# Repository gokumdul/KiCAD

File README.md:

# KiCAD
PCB sketch(.sch), and gerberData (.gbr)

- Project List
1. Simple LED and simple resistor
2. Multiple LEDs and multiple resistors
3. Fire alarm system

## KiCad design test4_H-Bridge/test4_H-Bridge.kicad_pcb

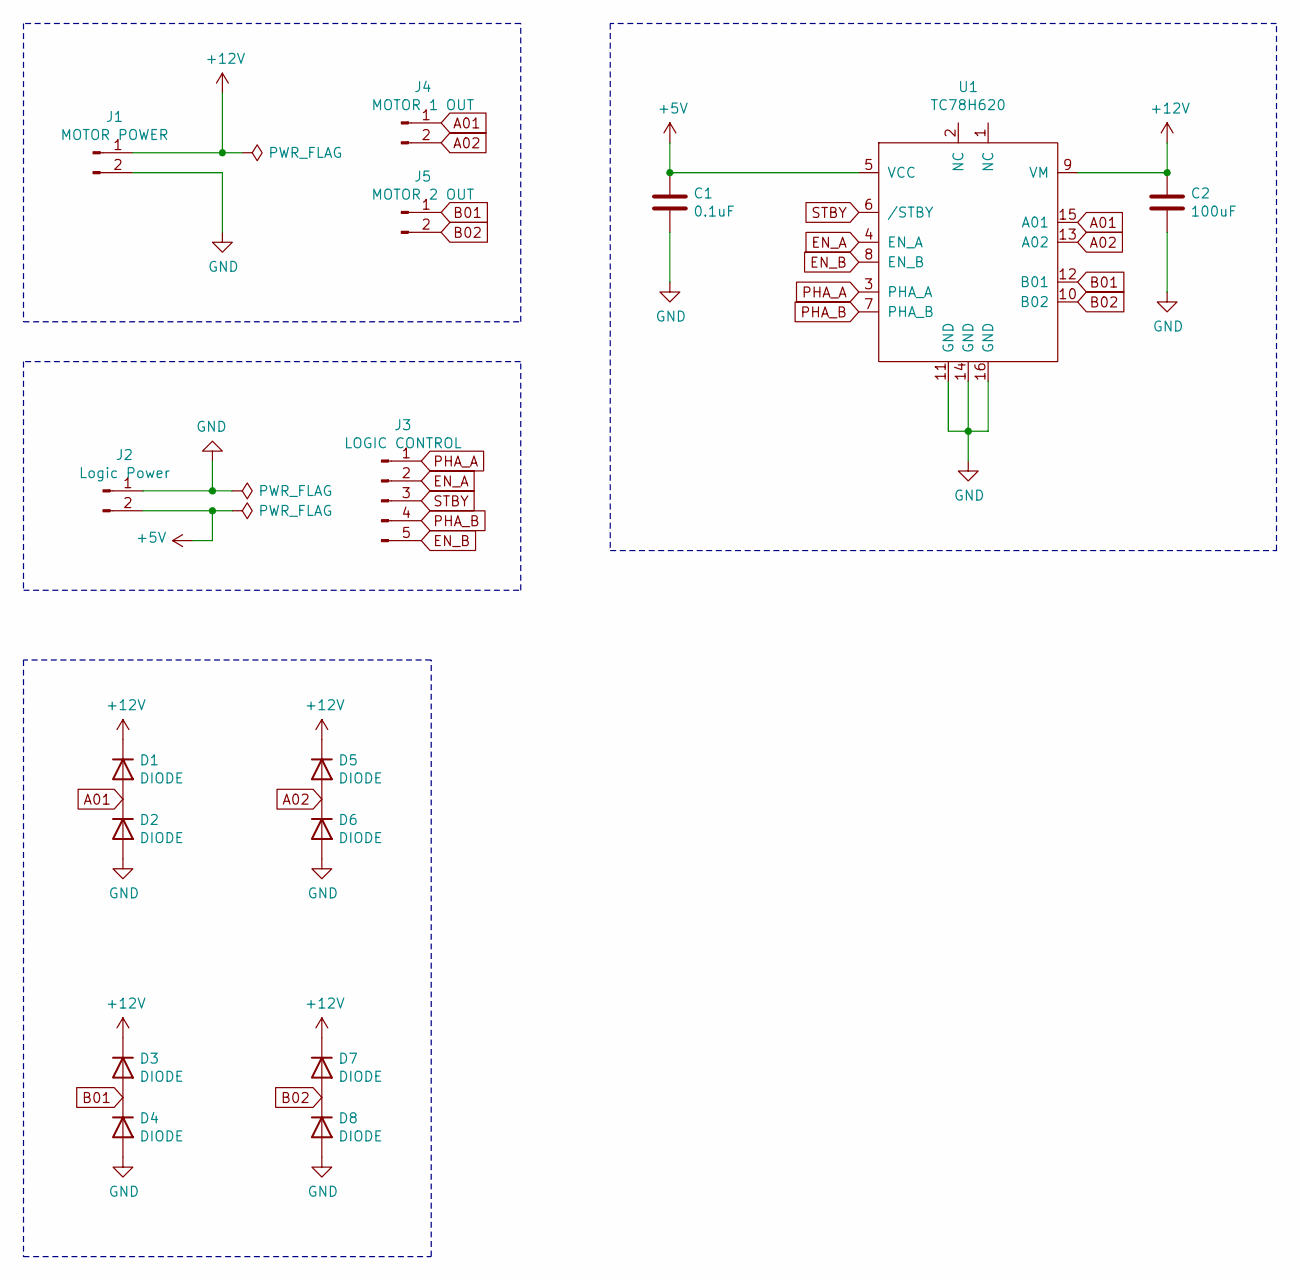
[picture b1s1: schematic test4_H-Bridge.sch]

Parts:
C1: 0.1uF
C2: 100uF
D1, D2, D3, D4, D5, D6, D7, D8: DIODE
J1: MOTOR POWER
J2: Logic Power
J3: LOGIC CONTROL
J4: MOTOR 1 OUT
J5: MOTOR 2 OUT
U1: TC78H620

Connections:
+5V: C1.2, J2.2, U1.5 (VCC)
+12V: C2.2, D1.2 (K), D3.2 (K), D5.2 (K), D7.2 (K), J1.1, U1.9 (VM)
A01: D1.1 (A), D2.2 (K), J4.1, U1.15 (A01)
A02: D5.1 (A), D6.2 (K), J4.2, U1.13 (A02)
B01: D3.1 (A), D4.2 (K), J5.1, U1.12 (B01)
B02: D7.1 (A), D8.2 (K), J5.2, U1.10 (B02)
EN_A: J3.2, U1.4 (EN_A)
EN_B: J3.5, U1.8 (EN_B)
GND: C1.1, C2.1, D2.1 (A), D4.1 (A), D6.1 (A), D8.1 (A), J1.2, J2.1, U1.11 (GND), U1.14 (GND), U1.16 (GND)
PHA_A: J3.1, U1.3 (PHA_A)
PHA_B: J3.4, U1.7 (PHA_B)
STBY: J3.3, U1.6 (/STBY)

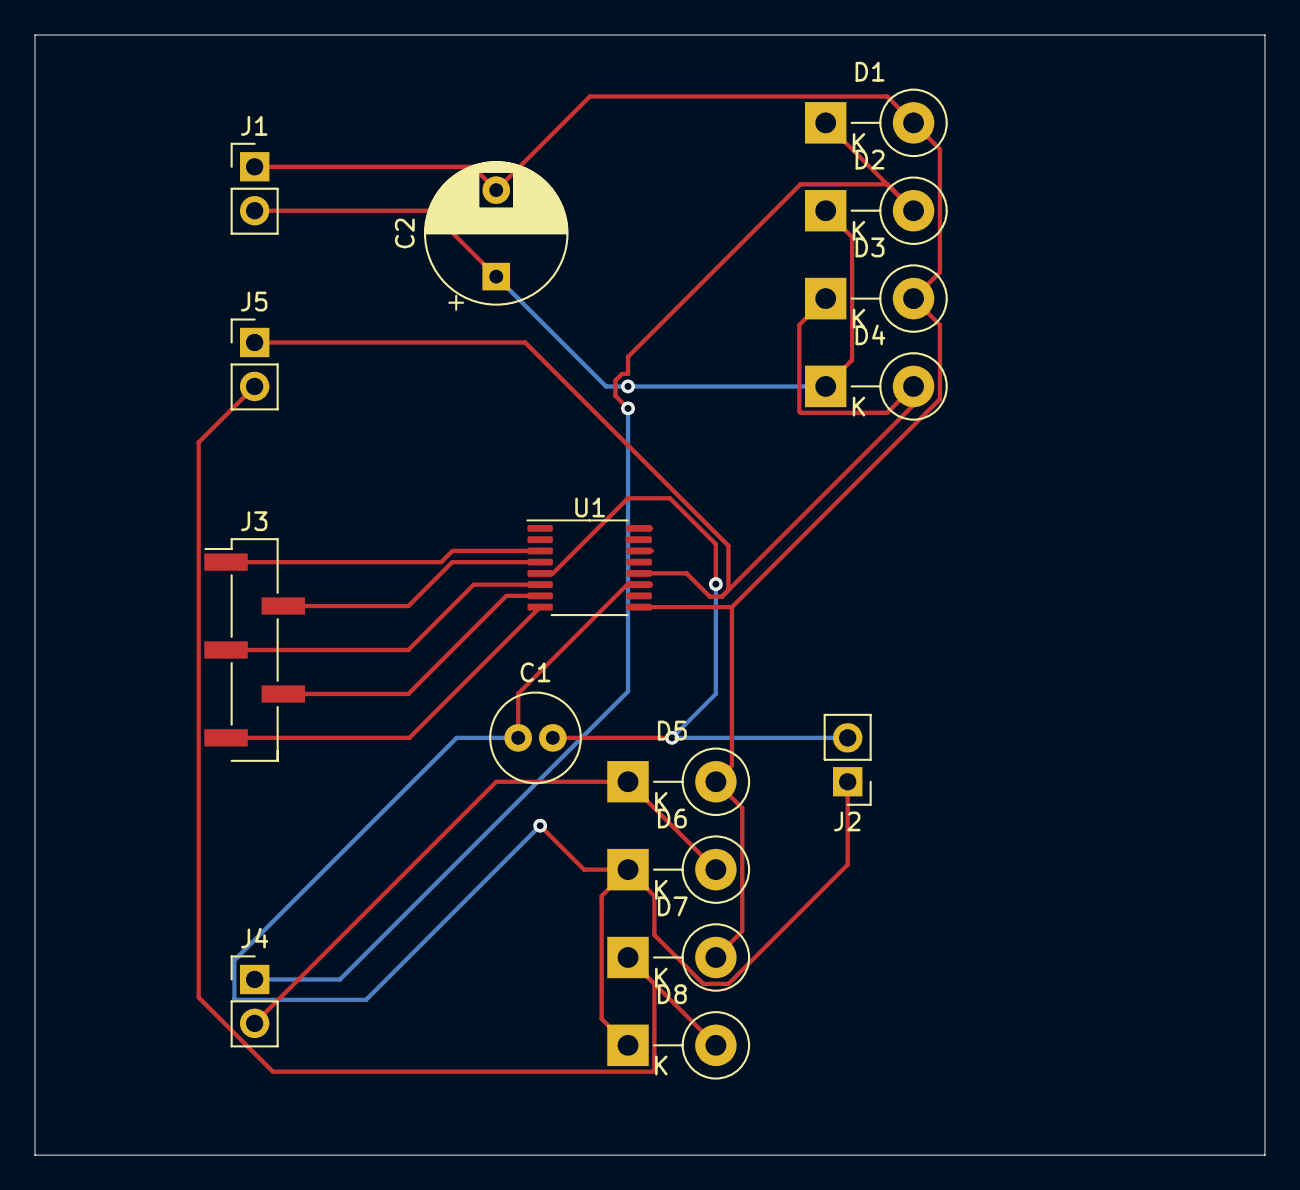
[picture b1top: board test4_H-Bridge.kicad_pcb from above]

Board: 2 copper layers, 71.1 x 64.8 mm, 16 parts (0 on the bottom side), 12 nets.

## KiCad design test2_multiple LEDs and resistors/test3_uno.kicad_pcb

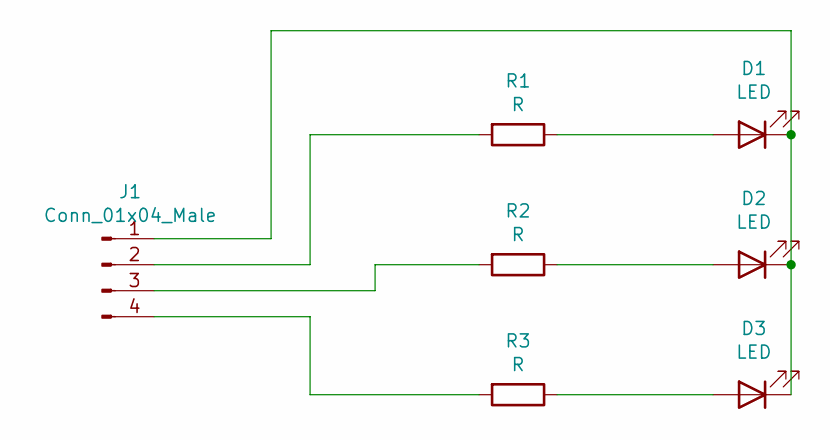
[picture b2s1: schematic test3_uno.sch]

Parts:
D1, D2, D3: LED; LED_D3.0mm
J1: Conn_01x04_Male; Molex_KK-396_A-41791-0004_1x04_P3.96mm_Vertical
R1, R2, R3: R; R_Axial_DIN0204_L3.6mm_D1.6mm_P5.08mm_Horizontal

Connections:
unnamed: D1.1 (K), D2.1 (K), D3.1 (K), J1.1
unnamed: D1.2 (A), R1.1
unnamed: D2.2 (A), R2.1
unnamed: D3.2 (A), R3.1
unnamed: J1.2, R1.2
unnamed: J1.3, R2.2
unnamed: J1.4, R3.2

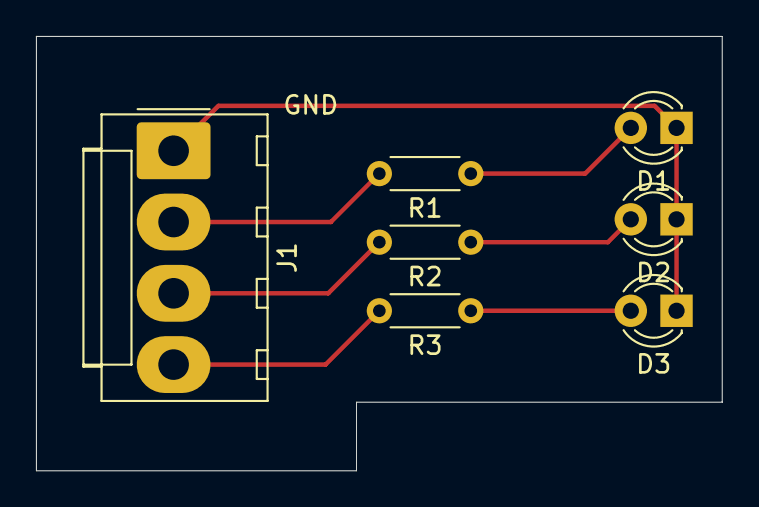
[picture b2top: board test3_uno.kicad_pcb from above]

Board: 2 copper layers, 38.1 x 24.1 mm, 7 parts (0 on the bottom side), 7 nets.

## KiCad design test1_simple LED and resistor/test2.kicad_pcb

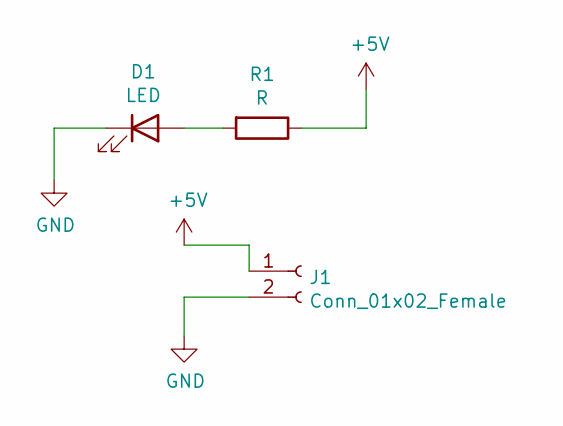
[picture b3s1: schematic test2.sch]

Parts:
D1: LED; LED_D3.0mm
J1: Conn_01x02_Female; Molex_KK-254_AE-6410-02A_1x02_P2.54mm_Vertical
R1: R; R_Axial_DIN0207_L6.3mm_D2.5mm_P7.62mm_Horizontal

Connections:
+5V: J1.1, R1.1
GND: D1.1 (K), J1.2
unnamed: D1.2 (A), R1.2

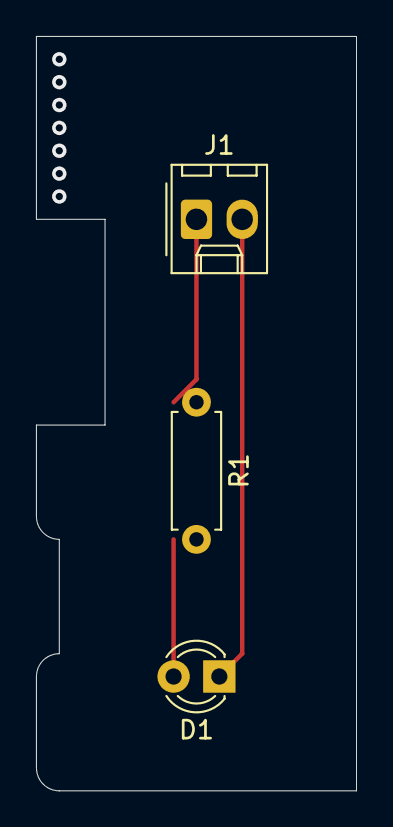
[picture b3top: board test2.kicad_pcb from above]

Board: 2 copper layers, 17.8 x 41.9 mm, 3 parts (0 on the bottom side), 3 nets.

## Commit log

2021-02-15 Add files via upload
    Project: Simple LED and resistor connection
    - parts:
    1. LED:
    - LED_THT: LED_D3.0mm
    2. Connector_Molex:
    - Molex_KK-254_AE-6410-02A_1x02_P2.54mm_Vertical
2021-02-15 test2_multiple LEDs and multiple resistors
    Project: multiple LEDs and multiple resistors
    - parts:
    1. LED:
    - LED_THT: LED_D3.0mm
    2. Connector_Molex:
    - Molex_KK-396_A-41791-0004_1x04_P3.96mm_Vertical
2021-02-15 Fire alarm system
    Info: Checking netlist symbol footprint "BZ1:/602A1309:Buzzer_Beeper:Buzzer_12x9.5RM7.6".
    Info: Checking netlist symbol footprint "C1:/602A0A52:Capacitor_THT:CP_Radial_D10.0mm_P3.50mm".
    Info: Checking netlist symbol footprint "D1:/6029F373:Diode_THT:D_5W_P10.16mm_Horizontal".
    Info: Checking netlist symbol footprint "J1:/602A27C1:Connector_BarrelJack:BarrelJack_Horizontal".
    Info: Checking netlist symbol footprint "Q1:/602A1E07:Package_TO_SOT_THT:TO-39-3".
    Info: Checking netlist symbol footprint "R1:/6029FC01:Resistor_THT:R_Axial_DIN0411_L9.9mm_D3.6mm_P12.70mm_Horizontal".
2021-02-17 test4_H-Bridge
    Info: Checking netlist symbol footprint "C1:/602D9DCF:Capacitor_THT:C_Radial_D5.0mm_H11.0mm_P2.00mm".
    Info: Checking netlist symbol footprint "C2:/602E69A4:Capacitor_THT:CP_Radial_D8.0mm_P5.00mm".
    Info: Checking netlist symbol footprint "D1:/602EDED8:Diode_THT:D_DO-15_P5.08mm_Vertical_KathodeUp".
    Info: Checking netlist symbol footprint "D2:/602F7EAB:Diode_THT:D_DO-15_P5.08mm_Vertical_KathodeUp".
    Info: Checking netlist symbol footprint "D3:/602F8FB5:Diode_THT:D_DO-15_P5.08mm_Vertical_KathodeUp".
    Info: Checking netlist symbol footprint "D4:/602FB1CE:Diode_THT:D_DO-15_P5.08mm_Vertical_KathodeUp".
